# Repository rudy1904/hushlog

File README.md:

# Hushlog

A 4-channel, 24-bit data logger for small, slow signals - thermocouples, strain
gauges, photodiodes, RTDs.

Most DIY loggers read tiny voltages with the microcontroller's built-in ADC,
which is fine until the signal is small, at which point it's mostly noise.
Hushlog uses a real 24-bit precision ADC (the TI ADS1220) with differential
input channels, read by a bare RP2040, logged to a microSD card, with a small
OLED for live readings - all on a custom 2-layer board.

The thing I care about most is keeping it **quiet**: a separate low-noise supply
for the analog side, RC filtering on every input, and a layout that keeps the
digital switching noise away from the ADC. The plan is to short the inputs,
measure the noise floor, and compare it to the datasheet - that number goes in
this repo, good or bad.

## Repo layout

| Folder | What's in it |
|---|---|
| `hardware/` | KiCad 10 project - schematic + PCB |
| `firmware/` | RP2040 test firmware (PlatformIO / Arduino-Pico) |
| `fab/` | Gerbers, drill files, placement, fabrication BOM |
| `docs/` | Schematic render and board images |
| `reports/` | ERC and DRC reports |

## Status

Design complete for the Hack Club Half Life warm-up (Tier 2).

- [x] RP2040 core - MCU, QSPI flash, crystal, USB-C + LDO power, BOOTSEL/RESET, SWD
- [x] ADS1220 analog front end - two differential channels, computed input
      filters, SPI0, separate low-noise LDO (AVDD isolated from the digital rail)
- [x] microSD (SPI1), OLED header (I2C1), status LED, UART debug header
- [x] PCB layout - 2-layer, analog/digital split, solid ground pour under the ADC

- [x] Test firmware - brings up ADC, SD, OLED, LED and UART
- [ ] Noise-floor measurement on real hardware

## Design choices

- **Bare RP2040, not a Pico module** - the MCU circuit is designed from scratch
  (reference design followed pin-for-pin so it boots first try).
- **External QSPI flash (W25Q128)** - the RP2040 has no internal flash.
- **Separate analog supply (TPS7A2033 LDO)** - the ADC gets its own low-noise
  supply fed from USB VBUS, so RP2040 switching noise never couples into the
  measurement.
- **Two differential input pairs** - suits small differential sensors
  (thermocouples, strain gauges) at high PGA gain, rather than single-ended.
- **2-layer board** - kept simple for a first build.

## Firmware

See [`firmware/README.md`](firmware/README.md). It's a bring-up test: it
configures the ADS1220, reads two differential channels, and streams the
readings over USB serial, SD and the OLED. Written for the Arduino-Pico core,
built with PlatformIO.

## Parts

Headline parts (full list in `BOM.md` and `fab/`):

| Part | Role |
|---|---|
| RP2040 | microcontroller |
| W25Q128 | QSPI boot flash |
| ADS1220 | 24-bit ADC |
| AP2112K-3.3 | 3.3V LDO (digital) |
| TPS7A2033 | low-noise LDO (analog) |
| SSD1306 0.96" | OLED display |

Note: SD writes and OLED refreshes should be held off during ADC conversions to
keep them out of the noise floor - handled in the real logging loop, flagged in
the firmware TODO.

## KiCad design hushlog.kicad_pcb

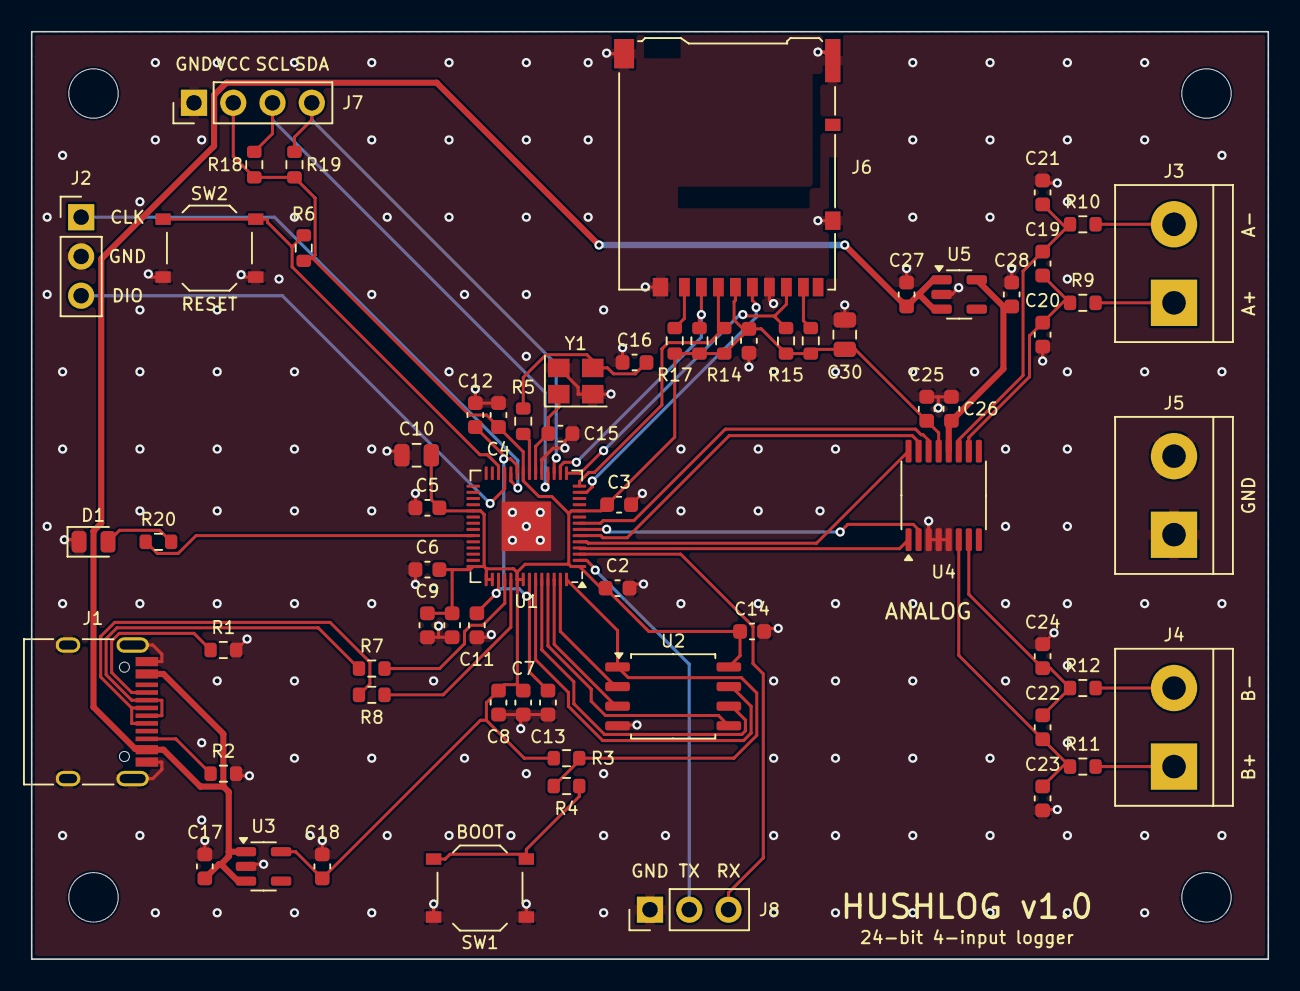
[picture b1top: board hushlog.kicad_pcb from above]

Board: 2 copper layers, 80.0 x 60.0 mm, 71 parts (0 on the bottom side), 49 nets.

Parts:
C1, C11, C17, C18, C27, C28: 1uF; C_0603_1608Metric
C2, C3, C4, C5, C6, C7, C8, C9, C12, C13, C14, C19, C22, C25, C26, C29: 100nF; C_0603_1608Metric
C10, C30: 10uF; C_0805_2012Metric
C15, C16: 15pF; C_0603_1608Metric
C20, C21, C23, C24: 10nF; C_0603_1608Metric
D1: LED; LED_0805_2012Metric
H1, H2, H3, H4: M3; MountingHole_3.2mm_M3
J1: USB_C_Receptacle_USB2.0_16P; USB_C_Receptacle_HRO_TYPE-C-31-M-12
J2: SWD; PinHeader_1x03_P2.54mm_Vertical
J3: IN_A; TerminalBlock_bornier-2_P5.08mm
J4: IN_B; TerminalBlock_bornier-2_P5.08mm
J5: GND; TerminalBlock_bornier-2_P5.08mm
J6: Micro_SD_Card; microSD_HC_Hirose_DM3AT-SF-PEJM5
J7: OLED; PinHeader_1x04_P2.54mm_Vertical
J8: UART; PinHeader_1x03_P2.54mm_Vertical
R1, R2: 5.1k; R_0603_1608Metric
R3, R6, R13, R14, R15, R16, R17: 10k; R_0603_1608Metric
R4, R5, R9, R10, R11, R12, R20: 1k; R_0603_1608Metric
R7, R8: 27R; R_0603_1608Metric
R18, R19: 4.7k; R_0603_1608Metric
SW1: BOOTSEL; SW_Push_1P1T_XKB_TS-1187A
SW2: RESET; SW_Push_1P1T_XKB_TS-1187A
U1: RP2040; QFN-56-1EP_7x7mm_P0.4mm_EP3.2x3.2mm
U2: W25Q128JVS; SOIC-8_5.3x5.3mm_P1.27mm
U3: AP2112K-3.3; SOT-23-5
U4: ADS1220IPW; TSSOP-16_4.4x5mm_P0.65mm
U5: TPS7A2033PDBV; SOT-23-5
Y1: 12MHz; Crystal_SMD_Abracon_ABM8G-4Pin_3.2x2.5mm

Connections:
+3.3V: C1.1, C2.1, C3.1, C4.1, C5.1, C6.1, C7.1, C8.1, C9.1, C10.1, C14.1, C18.1, C25.1, C29.1, C30.1, J6.4 (VDD), J7.2, R3.1, R6.1, R13.1, R14.1, R15.1, R16.1, R17.1, R18.1, R19.1, U1.1 (IOVDD), U1.10 (IOVDD), U1.22 (IOVDD), U1.33 (IOVDD), U1.42 (IOVDD), U1.43 (ADC_AVDD), U1.44 (VREG_VIN), U1.48 (USB_VDD), U1.49 (IOVDD), U2.8 (VCC), U3.5 (VOUT), U4.13 (DVDD)
+3.3VA: C26.1, C28.1, U4.12 (AVDD), U5.5 (OUT)
/+1V1: C11.1, C12.1, C13.1, U1.23 (DVDD), U1.45 (VREG_VOUT), U1.50 (DVDD)
/ADC_CS: U1.7 (GPIO5), U4.2 (~CS)
/ADC_DRDY: U1.8 (GPIO6), U4.14 (~DRDY)
/ADC_MISO: U1.6 (GPIO4), U4.15 (DOUT/~DRDY)
/ADC_MOSI: U1.5 (GPIO3), U4.16 (DIN)
/ADC_SCLK: U1.4 (GPIO2), U4.1 (SCLK)
/AIN0: C19.2, C21.1, R10.2, U4.11 (AIN0/REFP1)
/AIN1: C19.1, C20.2, R9.2, U4.10 (AIN1)
/AIN2: C22.2, C24.1, R12.2, U4.7 (AIN2)
/AIN3: C22.1, C23.2, R11.2, U4.6 (AIN3/REFN1)
/OLED_SCL: J7.3, R18.2, U1.18 (GPIO15)
/OLED_SDA: J7.4, R19.2, U1.17 (GPIO14)
/QSPI_SCLK: U1.52 (QSPI_SCLK), U2.6 (CLK)
/QSPI_SD0: U1.53 (QSPI_SD0), U2.5 (DI/IO_{0})
/QSPI_SD1: U1.55 (QSPI_SD1), U2.2 (DO/IO_{1})
/QSPI_SD2: U1.54 (QSPI_SD2), U2.3 (~WP/IO_{2})
/QSPI_SD3: U1.51 (QSPI_SD3), U2.7 (~HOLD/~RESET/IO_{3})
/QSPI_SS: R3.2, R4.1, U1.56 (~QSPI_SS), U2.1 (~CS)
/RUN: R6.2, SW2.1, U1.26 (RUN)
/SD_CS: J6.2 (DAT3/CD), R13.2, U1.16 (GPIO13)
/SD_DAT1: J6.8 (DAT1), R16.2
/SD_DAT2: J6.1 (DAT2), R17.2
/SD_MISO: J6.7 (DAT0), R15.2, U1.15 (GPIO12)
/SD_MOSI: J6.3 (CMD), R14.2, U1.14 (GPIO11)
/SD_SCLK: J6.5 (CLK), U1.13 (GPIO10)
/SWCLK: J2.1, U1.24 (SWCLK)
/SWDIO: J2.3, U1.25 (SWDIO)
/UART_RX: J8.3, U1.3 (GPIO1)
/UART_TX: J8.2, U1.2 (GPIO0)
/USB_CONN_D+: J1.A6 (D+), J1.B6 (D+), R8.1
/USB_CONN_D-: J1.A7 (D-), J1.B7 (D-), R7.1
/USB_D+: R8.2, U1.47 (USB_DP)
/USB_D-: R7.2, U1.46 (USB_DM)
/XIN: C15.1, U1.20 (XIN), Y1.1
/XOUT: R5.1, U1.21 (XOUT)
GND: C1.2, C2.2, C3.2, C4.2, C5.2, C6.2, C7.2, C8.2, C9.2, C10.2, C11.2, C12.2, C13.2, C14.2, C15.2, C16.2, C17.2, C18.2, C20.1, C21.2, C23.1, C24.2, C25.2, C26.2, C27.2, C28.2, C29.2, C30.2, D1.1 (K), J1.A1 (GND), J1.A12 (GND), J1.B1 (GND), J1.B12 (GND), J1.SH (SHIELD), J2.2, J5.1, J5.2, J6.6 (VSS), J6.SH (SHIELD), J7.1, J8.1, R1.2, R2.2, SW1.2, SW2.2, U1.19 (TESTEN), U1.57 (GND), U2.4 (GND), U3.2 (GND), U4.3 (CLK), U4.4 (DGND), U4.5 (AVSS), U5.2 (GND), Y1.2 (G), Y1.4 (G)
unnamed: C16.1, R5.2, Y1.3
unnamed: D1.2 (A), R20.2
unnamed: J1.A5 (CC1), R1.1
unnamed: J1.B5 (CC2), R2.1
unnamed: J3.1, R9.1
unnamed: J3.2, R10.1
unnamed: J4.1, R11.1
unnamed: J4.2, R12.1
unnamed: R4.2, SW1.1
unnamed: R20.1, U1.37 (GPIO25)
VBUS: C17.1, C27.1, J1.A4 (VBUS), J1.A9 (VBUS), J1.B4 (VBUS), J1.B9 (VBUS), U3.1 (VIN), U3.3 (EN), U5.1 (IN), U5.3 (EN)

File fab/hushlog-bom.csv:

References,Qty,Value,Footprint,Part,Manufacturer,LCSC (unverified),Unit price,Notes
C1 C11 C17 C18 C27 C28,6,1uF,C_0603_1608Metric,1uF 0603 capacitor,,,,"X7R, 10 V or more (C17/C27 sit on 5 V VBUS)"
C2 C3 C4 C5 C6 C7 C8 C9 C12 C13 C14 C19 C22 C25 C26 C29,16,100nF,C_0603_1608Metric,100nF 0603 capacitor,,,,X7R; C19/C22 (across the input pairs) are better as C0G/NP0 or film if the budget allows
C10 C30,2,10uF,C_0805_2012Metric,10uF 0805 capacitor,,,,"X5R/X7R, 10 V or more"
C15 C16,2,15pF,C_0603_1608Metric,15pF 0603 capacitor,,,,crystal load: C0G/NP0
C20 C21 C23 C24,4,10nF,C_0603_1608Metric,10nF 0603 capacitor,,,,input common-mode filter: use C0G/NP0
D1,1,LED,LED_0805_2012Metric,0805 green LED,,,,
J1,1,USB_C_Receptacle_USB2.0_16P,USB_C_Receptacle_HRO_TYPE-C-31-M-12,TYPE-C-31-M-12,Korean Hroparts,C165948,,16-pin USB 2.0 receptacle
J2,1,SWD,PinHeader_1x03_P2.54mm_Vertical,1x3 2.54 mm header,,,,
J3,1,IN_A,TerminalBlock_bornier-2_P5.08mm,2-way 5.08 mm screw terminal,,,,
J4,1,IN_B,TerminalBlock_bornier-2_P5.08mm,2-way 5.08 mm screw terminal,,,,
J5,1,GND,TerminalBlock_bornier-2_P5.08mm,2-way 5.08 mm screw terminal,,,,
J6,1,Micro_SD_Card,microSD_HC_Hirose_DM3AT-SF-PEJM5,DM3AT-SF-PEJM5,Hirose,C114218,,push-push; footprint is for this exact part
J7,1,OLED,PinHeader_1x04_P2.54mm_Vertical,1x4 2.54 mm header (or socket),,,,"for a 0.96 in SSD1306 I2C module, pin order GND-VCC-SCL-SDA"
J8,1,UART,PinHeader_1x03_P2.54mm_Vertical,1x3 2.54 mm header,,,,
R1 R2,2,5.1k,R_0603_1608Metric,5.1k 0603 resistor 1%,,,,
R3 R6 R13 R14 R15 R16 R17,7,10k,R_0603_1608Metric,10k 0603 resistor 1%,,,,
R4 R5 R9 R10 R11 R12 R20,7,1k,R_0603_1608Metric,1k 0603 resistor 1%,,,,
R7 R8,2,27R,R_0603_1608Metric,27R 0603 resistor 1%,,,,
R18 R19,2,4.7k,R_0603_1608Metric,4.7k 0603 resistor 1%,,,,
SW1,1,BOOTSEL,SW_Push_1P1T_XKB_TS-1187A,TS-1187A-B-A-B,XKB,C318884,,tactile switch 5.1x5.1 mm
SW2,1,RESET,SW_Push_1P1T_XKB_TS-1187A,TS-1187A-B-A-B,XKB,C318884,,tactile switch 5.1x5.1 mm
U1,1,RP2040,QFN-56-1EP_7x7mm_P0.4mm_EP3.2x3.2mm,RP2040,Raspberry Pi,C2040,,
U2,1,W25Q128JVS,SOIC-8_5.3x5.3mm_P1.27mm,W25Q128JVSIQ,Winbond,C97521,,SOIC-8 208 mil
U3,1,AP2112K-3.3,SOT-23-5,AP2112K-3.3TRG1,Diodes Inc.,C51118,,
U4,1,ADS1220IPW,TSSOP-16_4.4x5mm_P0.65mm,ADS1220IPWR,Texas Instruments,,,TSSOP-16
U5,1,TPS7A2033PDBV,SOT-23-5,TPS7A2033PDBVR,Texas Instruments,,,3.3 V low-noise LDO
Y1,1,12MHz,Crystal_SMD_Abracon_ABM8G-4Pin_3.2x2.5mm,ABM8-272-T3,Abracon,,,"12 MHz, CL 10 pF, 3.2x2.5 mm; recalculate C15/C16 for any other crystal"
(not on the board),1,OLED module,,0.96 in SSD1306 I2C module,,,,check its pin order against J7
(not on the board),1,PCB,,"80 x 60 mm, 2 layers, 1.6 mm",,,,

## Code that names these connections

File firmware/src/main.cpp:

/*
 * Hushlog - test firmware
 * ------------------------
 * Brings up each peripheral on the board and proves it works:
 *   - ADS1220 24-bit ADC over SPI0  (reads 2 differential channels)
 *   - microSD card over SPI1        (logs timestamped samples as CSV)
 *   - SSD1306 OLED over I2C1        (shows live readings)
 *   - status LED on GPIO25          (heartbeat + SD-error indicator)
 *   - USB serial / UART             (prints every sample for debugging)
 *
 * Target: RP2040, built with the Arduino-Pico core (earlephilhower).
 *
 * This is a bring-up test, not a finished logger. It reads the ADC with
 * the PGA at a fixed gain, prints and logs the raw code and the voltage,
 * and does nothing clever with timing yet. The point is to confirm every
 * chip on the board responds before writing the real logging loop.
 *
 * Pin map (from the Hushlog schematic):
 *   ADS1220 (SPI0):  SCLK=GPIO2  MOSI=GPIO3  MISO=GPIO4  CS=GPIO5  DRDY=GPIO6
 *   microSD (SPI1):  SCLK=GPIO10 MOSI=GPIO11 MISO=GPIO12 CS=GPIO13
 *   OLED    (I2C1):  SDA=GPIO14  SCL=GPIO15
 *   status LED:      GPIO25
 *   UART0 debug:     TX=GPIO0    RX=GPIO1
 */

#include <Arduino.h>
#include <SPI.h>
#include <Wire.h>
#include <SdFat.h>
#include <Adafruit_GFX.h>
#include <Adafruit_SSD1306.h>

// ---------- pin definitions ----------
#define ADC_SCLK   2
#define ADC_MOSI   3
#define ADC_MISO   4
#define ADC_CS     5
#define ADC_DRDY   6

#define SD_SCLK   10
#define SD_MOSI   11
#define SD_MISO   12
#define SD_CS     13

#define OLED_SDA  14
#define OLED_SCL  15

#define LED_PIN   25

// ---------- ADS1220 commands (datasheet table 15) ----------
#define ADS1220_CMD_RESET   0x06
#define ADS1220_CMD_START   0x08
#define ADS1220_CMD_RDATA   0x10
#define ADS1220_CMD_WREG    0x40
#define ADS1220_CMD_RREG    0x20

// SPI mode 1 (CPOL=0, CPHA=1), MSB first, <= 4 MHz for the ADS1220.
SPISettings adcSpi(1000000, MSBFIRST, SPI_MODE1);

#define OLED_W 128
#define OLED_H 64
Adafruit_SSD1306 oled(OLED_W, OLED_H, &Wire1, -1);

SdFat sd;
SdFile logFile;
bool sdOK = false;

// Internal reference 2.048 V; full-scale code is +/- 2^23.
const float VREF = 2.048f;
const float FULL_SCALE = 8388608.0f;

void adcWriteReg(uint8_t reg, uint8_t value) {
  SPI.beginTransaction(adcSpi);
  digitalWrite(ADC_CS, LOW);
  SPI.transfer(ADS1220_CMD_WREG | (reg << 2) | 0x00);
  SPI.transfer(value);
  digitalWrite(ADC_CS, HIGH);
  SPI.endTransaction();
}

uint8_t adcReadReg(uint8_t reg) {
  SPI.beginTransaction(adcSpi);
  digitalWrite(ADC_CS, LOW);
  SPI.transfer(ADS1220_CMD_RREG | (reg << 2) | 0x00);
  uint8_t v = SPI.transfer(0xFF);
  digitalWrite(ADC_CS, HIGH);
  SPI.endTransaction();
  return v;
}

void adcCommand(uint8_t cmd) {
  SPI.beginTransaction(adcSpi);
  digitalWrite(ADC_CS, LOW);
  SPI.transfer(cmd);
  digitalWrite(ADC_CS, HIGH);
  SPI.endTransaction();
}

int32_t adcReadData() {
  SPI.beginTransaction(adcSpi);
  digitalWrite(ADC_CS, LOW);
  SPI.transfer(ADS1220_CMD_RDATA);
  uint8_t b2 = SPI.transfer(0xFF);
  uint8_t b1 = SPI.transfer(0xFF);
  uint8_t b0 = SPI.transfer(0xFF);
  digitalWrite(ADC_CS, HIGH);
  SPI.endTransaction();
  int32_t raw = ((int32_t)b2 << 16) | ((int32_t)b1 << 8) | b0;
  if (raw & 0x800000) raw |= 0xFF000000; // sign-extend 24->32
  return raw;
}

void adcConfigure() {
  adcCommand(ADS1220_CMD_RESET);
  delay(1);
  adcWriteReg(0x00, 0x00); // MUX=AIN0-AIN1, gain 1, PGA enabled
  adcWriteReg(0x01, 0x00); // 20 SPS, single-shot
  adcWriteReg(0x02, 0x00); // internal 2.048V ref
  adcWriteReg(0x03, 0x00);
}

void adcSetChannel(uint8_t pair) {
  uint8_t mux = (pair == 0) ? 0x00 : 0x50; // AIN0/AIN1 or AIN2/AIN3
  uint8_t reg0 = adcReadReg(0x00) & 0x0F;
  adcWriteReg(0x00, mux | reg0);
}

int32_t adcReadChannel(uint8_t pair) {
  adcSetChannel(pair);
  adcCommand(ADS1220_CMD_START);
  uint32_t t0 = millis();
  while (digitalRead(ADC_DRDY) == HIGH) {
    if (millis() - t0 > 100) break;
  }
  return adcReadData();
}

float codeToVolts(int32_t code) {
  return ((float)code / FULL_SCALE) * VREF;
}

void setup() {
  pinMode(LED_PIN, OUTPUT);
  digitalWrite(LED_PIN, HIGH);

  Serial.begin(115200);
  uint32_t t0 = millis();
  while (!Serial && millis() - t0 < 2000) { }
  Serial.println();
  Serial.println("Hushlog test firmware starting...");

  // ADS1220 on SPI0
  SPI.setSCK(ADC_SCLK);
  SPI.setTX(ADC_MOSI);
  SPI.setRX(ADC_MISO);
  pinMode(ADC_CS, OUTPUT);
  digitalWrite(ADC_CS, HIGH);
  pinMode(ADC_DRDY, INPUT);
  SPI.begin();
  adcConfigure();
  uint8_t reg0 = adcReadReg(0x00);
  Serial.print("ADS1220 reg0 readback: 0x");
  Serial.println(reg0, HEX);
  Serial.println(reg0 == 0x00 ? "  ADC responding." : "  ADC NOT responding - check wiring/CS.");

  // OLED on I2C1
  Wire1.setSDA(OLED_SDA);
  Wire1.setSCL(OLED_SCL);
  Wire1.begin();
  if (oled.begin(SSD1306_SWITCHCAPVCC, 0x3C)) {
    oled.clearDisplay();
    oled.setTextSize(1);
    oled.setTextColor(SSD1306_WHITE);
    oled.setCursor(0, 0);
    oled.println("Hushlog");
    oled.println("booting...");
    oled.display();
    Serial.println("OLED OK.");
  } else {
    Serial.println("OLED NOT found at 0x3C.");
  }

  // microSD on SPI1
  SPI1.setSCK(SD_SCLK);
  SPI1.setTX(SD_MOSI);
  SPI1.setRX(SD_MISO);
  SdSpiConfig cfg(SD_CS, DEDICATED_SPI, SD_SCK_MHZ(8), &SPI1);
  if (sd.begin(cfg)) {
    sdOK = true;
    if (logFile.open("hushlog.csv", O_WRITE | O_CREAT | O_APPEND)) {
      logFile.println("millis,ch0_code,ch0_volts,ch1_code,ch1_volts");
      logFile.sync();
    }
    Serial.println("SD OK, logging to hushlog.csv");
  } else {
    Serial.println("SD NOT found - will print only, no logging.");
  }

  digitalWrite(LED_PIN, LOW);
  Serial.println("Setup done. Reading...");
  Serial.println("millis,ch0_code,ch0_volts,ch1_code,ch1_volts");
}

void loop() {
  digitalWrite(LED_PIN, HIGH);

  int32_t c0 = adcReadChannel(0);
  int32_t c1 = adcReadChannel(1);
  float v0 = codeToVolts(c0);
  float v1 = codeToVolts(c1);
  uint32_t ts = millis();

  Serial.print(ts);   Serial.print(',');
  Serial.print(c0);   Serial.print(',');
  Serial.print(v0, 6); Serial.print(',');
  Serial.print(c1);   Serial.print(',');
  Serial.println(v1, 6);

  if (sdOK) {
    logFile.print(ts);   logFile.print(',');
    logFile.print(c0);   logFile.print(',');
    logFile.print(v0, 6); logFile.print(',');
    logFile.print(c1);   logFile.print(',');
    logFile.println(v1, 6);
    logFile.sync();
  } else {
    digitalWrite(LED_PIN, LOW); delay(80);
    digitalWrite(LED_PIN, HIGH); delay(80);
  }

  oled.clearDisplay();
  oled.setCursor(0, 0);
  oled.println("Hushlog");
  oled.print("CH0 "); oled.print(v0, 4); oled.println(" V");
  oled.print("CH1 "); oled.print(v1, 4); oled.println(" V");
  oled.print(sdOK ? "SD: logging" : "SD: none");
  oled.display();

  digitalWrite(LED_PIN, LOW);
  delay(500);
}
